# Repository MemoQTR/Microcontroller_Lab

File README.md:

# MicrocontrollerLaboratory

## Introduction

Microcontrollers are all around  he world. Each day, Microcontrollers, are more present in the many aspects of our lives: in our work, inside our houses, and in more. We can find them controlling small devices like cellphones, microwaves, washing machines, and televisions.

A microcontroller is one device or chip that is used to govern one or more processes. For example, the controller that regulates the room temperature of an air conditioner; it has a sensor that continuously measures the internal temperature and, when the preset limits are exceeded, it generates the necessary signals to adjust the temperature.

## State of the Art

### The practices and the PIC microcontroller

The main objective of this practices is to provide students the foundation to fully understand the operation of the PIC18F45K50 microcontroller. This will be achieved through 11 documents that will guide the reader to create their own electronic card or Printed Circuit Board (PCB) and to be able to program it; in order to, execute different functions.

The advantages of ta PIC microcontroller to others on the market, which is why it will be used throughout this manual, are as follows:

- Easy to operate.
- There is enough documentation to work with it and it’s easy to obtain it.
- The price is comparatively lower than its competitors.
- It has a high operating speed.
- Development tools are cheap and easy to use.
- There are a variety of hardware that can record, erase and check the behavior of PIC.
- Once you learn to handle a PIC, it will easier to handle any other models of microcontrollers.

### KiCad EDA Software

KiCad is an open source software suite for Electronic Design Automation (EDA). The programs handle Schematic Capture,
and PCB Layout with Gerber output. The suite runs on Windows, Linux and macOS and is licensed under GNU GPL v3. The
first release date was in 1992 by its original author, Jean-Pierre Charras, but is now currently under development by
the KiCad Developers Team.

## Evaluation

- Demonstation  ... 60%
- Report .......... 40%

## Submission

Every submission must be in your own github repository. If you which you could fork this as skeleton. All pull request
will be denied.

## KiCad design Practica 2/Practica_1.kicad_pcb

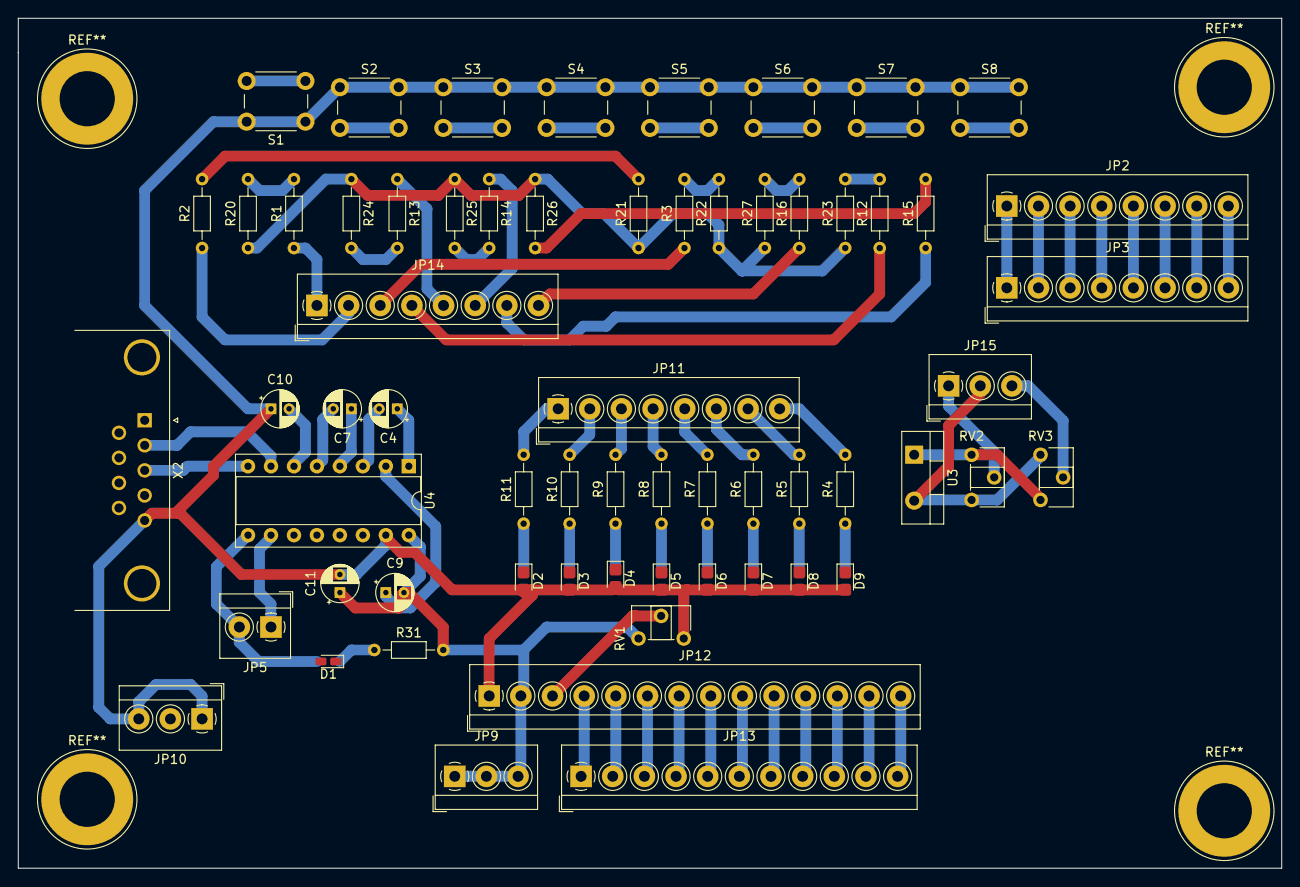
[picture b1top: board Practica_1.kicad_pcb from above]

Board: 2 copper layers, 139.7 x 94.0 mm, 63 parts (0 on the bottom side), 71 nets.

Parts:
C4, C7, C9, C10, C11: 10u; CP_Radial_D4.0mm_P2.00mm
D1: LED; LED_0603_1608Metric_Castellated
D2, D3, D4, D5, D6, D7, D8, D9: LED; LED_0805_2012Metric_Castellated
JP2, JP3, JP11, JP14: PINHD-1X8; TerminalBlock_4Ucon_1x08_P3.50mm_Horizontal
JP5: PINHD-1X2; TerminalBlock_4Ucon_1x02_P3.50mm_Horizontal
JP9, JP10, JP15: PINHD-1X3; TerminalBlock_4Ucon_1x03_P3.50mm_Horizontal
JP12: PINHD-1X14M; TerminalBlock_4Ucon_1x14_P3.50mm_Horizontal
JP13: PINHD-1X11; TerminalBlock_4Ucon_1x11_P3.50mm_Horizontal
R1, R2, R3, R12, R13, R14, R15, R16: 1k; R_Axial_DIN0204_L3.6mm_D1.6mm_P7.62mm_Horizontal
R4, R5, R6, R7, R8, R9, R10, R11, R31: 470; R_Axial_DIN0204_L3.6mm_D1.6mm_P7.62mm_Horizontal
R20: 4.7K; R_Axial_DIN0204_L3.6mm_D1.6mm_P7.62mm_Horizontal
R21, R22, R23, R24, R25, R26, R27: 4.7k; R_Axial_DIN0204_L3.6mm_D1.6mm_P7.62mm_Horizontal
RV1, RV2, RV3: 10k; Potentiometer_ACP_CA6-H2,5_Horizontal
S1, S2, S3, S4, S5, S6, S7, S8: DIS-6; SW_PUSH_6mm
U3: MCP9700A; TO-220-2_Vertical
U4: MAX232; DIP-16_W7.62mm_Socket
X2: F09HP; DSUB-9_Male_Horizontal_P2.77x2.84mm_EdgePinOffset4.94mm_Hou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

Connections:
+5V: RV2.1, RV3.3, U3.1
+5VA: C9.2, C11.1, JP9.1, JP9.2, JP9.3, JP12.2, R31.2, RV1.1, U4.16
GND: RV2.3, RV3.1
GNDA: C10.1, C11.2, D2.2, D3.2, D4.2, D5.2, D6.2, D7.2, D8.2, D9.2, JP10.1, JP10.2, JP10.3, JP12.1, RV1.3, S1.1, S2.1, S3.1, S4.1, S5.1, S6.1, S7.1, S8.1, U4.15, X2.5
unnamed: C4.1, U4.1
unnamed: C4.2, U4.3
unnamed: C7.1, U4.4
unnamed: C7.2, U4.5
unnamed: C9.1, U4.2
unnamed: C10.2, U4.6
unnamed: D1.1, R31.1
unnamed: D1.2, JP5.2, U4.9
unnamed: D2.1, R11.1
unnamed: D3.1, R10.1
unnamed: D4.1, R9.1
unnamed: D5.1, R8.1
unnamed: D6.1, R7.1
unnamed: D7.1, R6.1
unnamed: D8.1, R5.1
unnamed: D9.1, R4.1
unnamed: JP2.1, JP3.1
unnamed: JP2.2, JP3.2
unnamed: JP2.3, JP3.3
unnamed: JP2.4, JP3.4
unnamed: JP2.5, JP3.5
unnamed: JP2.6, JP3.6
unnamed: JP2.7, JP3.7
unnamed: JP2.8, JP3.8
unnamed: JP5.1, U4.10
unnamed: JP11.1, R11.2
unnamed: JP11.2, R10.2
unnamed: JP11.3, R9.2
unnamed: JP11.4, R8.2
unnamed: JP11.5, R7.2
unnamed: JP11.6, R6.2
unnamed: JP11.7, R5.2
unnamed: JP11.8, R4.2
unnamed: JP12.3, RV1.2
unnamed: JP12.4, JP13.1
unnamed: JP12.5, JP13.2
unnamed: JP12.6, JP13.3
unnamed: JP12.7, JP13.4
unnamed: JP12.8, JP13.5
unnamed: JP12.9, JP13.6
unnamed: JP12.10, JP13.7
unnamed: JP12.11, JP13.8
unnamed: JP12.12, JP13.9
unnamed: JP12.13, JP13.10
unnamed: JP12.14, JP13.11
unnamed: JP14.1, R1.1
unnamed: JP14.2, R2.1
unnamed: JP14.3, R3.1
unnamed: JP14.4, R12.1
unnamed: JP14.5, R13.1
unnamed: JP14.6, R14.1
unnamed: JP14.7, R15.1
unnamed: JP14.8, R16.1
unnamed: JP15.1, RV2.2
unnamed: JP15.2, U3.2
unnamed: JP15.3, RV3.2
unnamed: R1.2, R20.2
unnamed: R2.2, R21.2
unnamed: R12.2, R23.2
unnamed: R13.2, R24.2
unnamed: R14.2, R25.2
unnamed: R15.2, R26.2
unnamed: R16.2, R27.2
unnamed: R20.1, R21.1, R22.1, R23.1, R24.1, R25.1, R26.1, R27.1
unnamed: R3.2, R22.2
unnamed: U4.7, X2.2
unnamed: U4.8, X2.3

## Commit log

2020-08-18 Create repository
2020-09-16 Create Practica 1
2020-10-29 Rename LINK.md to VIDEO_LINK.md
2020-10-30 Rename practica 4/ElementoUnico.c to practica 4/e/ElementoUnico.c
2020-10-30 Rename practica 4/GreyCode.c to practica 4/C files/GreyCode.c
2020-10-30 Rename practica 4/Multiplicaciones y divisiones.c to practica 4/C files/Multiplicaciones y divisiones.c
2020-10-30 Rename practica 4/Potencias.c to practica 4/C files/Potencias.c
